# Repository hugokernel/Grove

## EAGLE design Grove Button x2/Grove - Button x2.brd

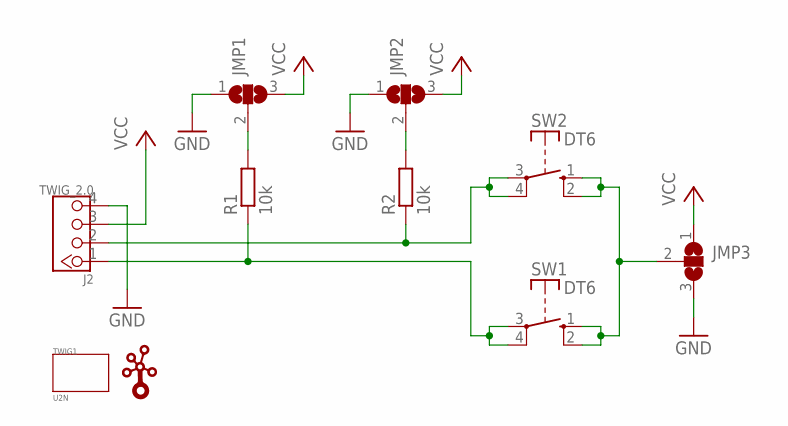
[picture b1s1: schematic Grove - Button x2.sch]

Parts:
J2: TWIG_2.0; 2.0_1X4
JMP1, JMP2, JMP3: SJ2W; SJ_2
R1, R2: 10k; R0805
SW1, SW2: DT6
TWIG1: U2N
U$1: TWIGLOGOTWIGLOGO_SMALL; TWIGLOGO_SMALL

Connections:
GND: J2.4, JMP1.1, JMP2.1, JMP3.3
unnamed: J2.2, R2.1, SW2.3, SW2.4
unnamed: J2.1, R1.1, SW1.3, SW1.4
unnamed: JMP2.2, R2.2
unnamed: JMP3.2, SW1.1 (S), SW1.2 (S), SW2.1 (S), SW2.2 (S)
unnamed: JMP1.2, R1.2
VCC: J2.3, JMP1.3, JMP2.3, JMP3.1

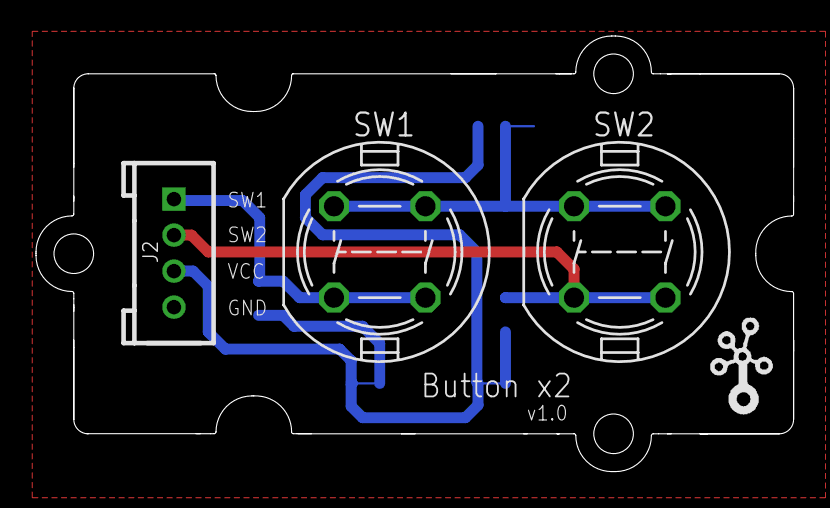
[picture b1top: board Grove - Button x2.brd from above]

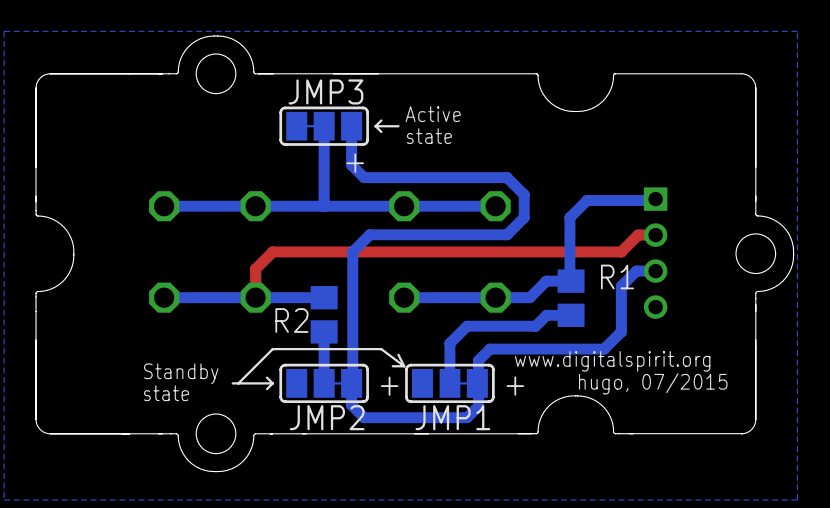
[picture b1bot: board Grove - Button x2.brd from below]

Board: 2 copper layers, 42.1 x 24.2 mm, 10 parts (5 on the bottom side), 7 nets.

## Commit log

2015-07-17 Button x2
    Grove module with 2 button.
    Standby state and active state configurable with jumper.
2015-07-17 Help
    Some help on board
